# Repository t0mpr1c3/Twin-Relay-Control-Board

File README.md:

Twin-Relay-Control-Board
========================

Control board for two NAIS JSM1A or Songle SRD NO relays on Dangerous Prototypes DP5050 standard PCB size.

Derived from Sparkfun Electronics COM-11041 designed by N. Seidle and Joel Bartlett.

The component values are designed for VCC = 5 VDC. For VCC = 12 VDC, R4/R5 = 3.3K.

Released under Creative Commons Attribution Share-Alike 3.0 License. http://creativecommons.org/licenses/by-sa/3.0

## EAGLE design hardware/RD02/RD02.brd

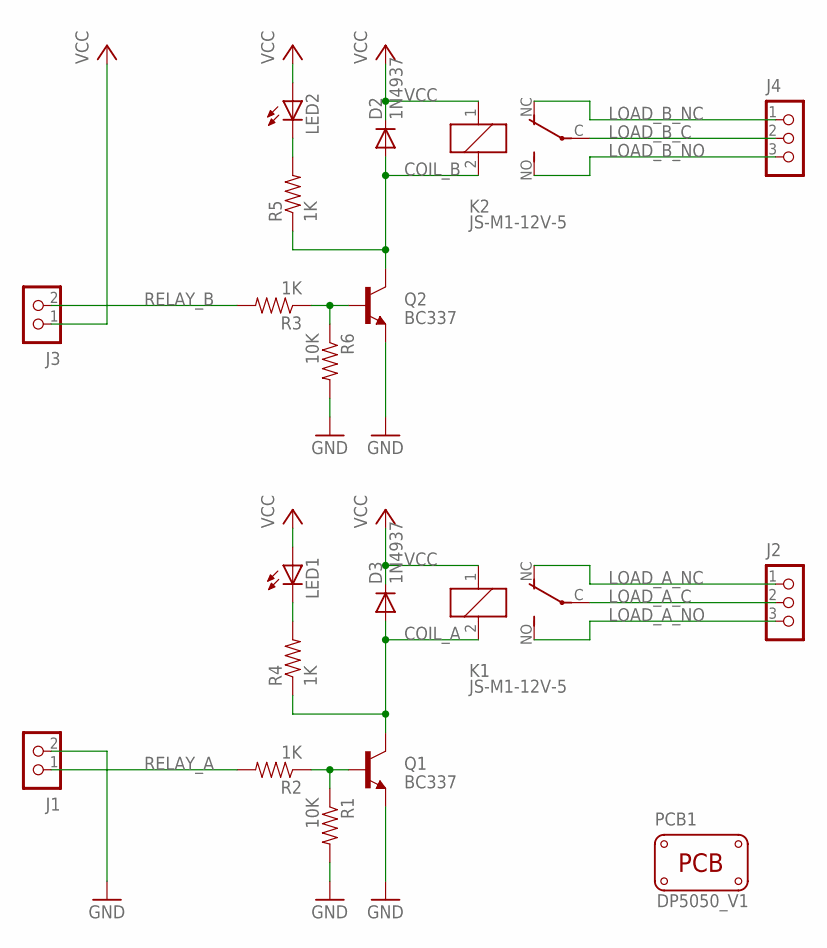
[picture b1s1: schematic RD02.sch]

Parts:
D2, D3: 1N4937; DO41-10
J1, J3: CON_TERMINAL_BLOCK_02-5MM; TERMINAL_BLOCK_2P_5
J2, J4: CON_TERMINAL_BLOCK_03-5MM; TERMINAL_BLOCK_3P_5
K1, K2: JS-M1-12V-5; JS-M; MPN JSM1-12V-5
LED1, LED2: LED-3MM
PCB1: PCB_DP_SQUARE-5X5; DP5050_V1
Q1, Q2: BC337; TO92
R1, R6: 10K; AXIAL-0.3
R2, R3, R4, R5: 1K; AXIAL-0.3

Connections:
COIL_A: D3.A, K1.2, Q1.3 (C), R4.P$1 (1)
COIL_B: D2.A, K2.2, Q2.3 (C), R5.P$1 (1)
GND: J1.2, Q1.1 (E), Q2.1 (E), R1.P$2 (2), R6.P$2 (2)
LOAD_A_C: J2.2, K1.C
LOAD_A_NC: J2.1, K1.NC (O)
LOAD_A_NO: J2.3, K1.NO (S)
LOAD_B_C: J4.2, K2.C
LOAD_B_NC: J4.1, K2.NC (O)
LOAD_B_NO: J4.3, K2.NO (S)
unnamed: Q2.2 (B), R3.P$1 (1), R6.P$1 (1)
unnamed: LED2.K (C), R5.P$2 (2)
unnamed: Q1.2 (B), R1.P$1 (1), R2.P$1 (1)
unnamed: LED1.K (C), R4.P$2 (2)
RELAY_A: J1.1, R2.P$2 (2)
RELAY_B: J3.2, R3.P$2 (2)
VCC: D2.C, D3.C, J3.1, K1.1, K2.1, LED1.A, LED2.A

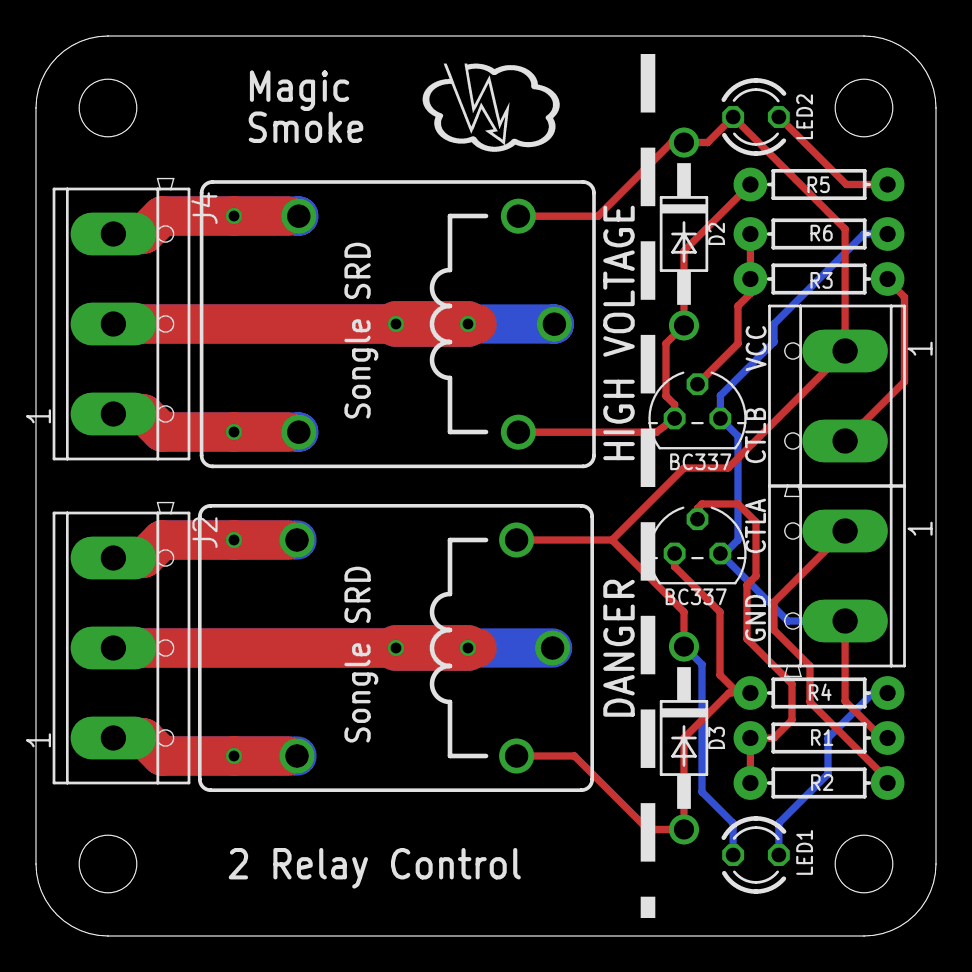
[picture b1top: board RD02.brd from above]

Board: 4 copper layers, 50.0 x 50.0 mm, 20 parts (1 on the bottom side), 16 nets.

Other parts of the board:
U$2: OSHW-LOGO-M

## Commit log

2013-11-23 RB02 first draft
2013-11-23 BC337s instead of BC546s
2013-11-24 logo
2013-11-25 tweak gerbers
2013-11-26 JS-M1 relay package
2013-11-30 reorganize folders
2013-12-03 2mm clearance
2013-12-05 RD01 Elecrow order
2013-12-07 faster higher power diode closer to coil

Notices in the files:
hardware/RD02/RD02.brd:
CC BY-SA 3.0
